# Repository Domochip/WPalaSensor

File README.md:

# WPalaSensor

This project aims to replace the Palazzetti (Fumis) room temperature sensor by an electronic simulator.  
It allows you to push home automation temperature to the stove.  
You can then keep native modulation that reduce power automatically when desired temperature is reached.  

## Compatibility

It appears that Fumis Controller is used by those brands for their stoves : 

* Palazzetti (All)
* Jotul
* TurboFonte
* Godin
* Fonte Flamme
* Invicta

If you have this controller in your stove, it's likely to be compatible.  

## Build your adapter

All files are inside `schematic` subfolder and has been designed with KiCad (free and open source)

### Schematic

### PCB

*We produced a small batch of this adapter for test/debugging and our personal use.
If you are interested, please PM.*

### Print your box

Box project (Fusion 360 & STL) can be found into `box` folder

### Code/Compile/Flash

Source code can be compiled using VisualStudioCode/Platformio and flashed onto a D1 Mini  
Or  
Download latest release in Release section

### Connect

⚠️To connect WPalaSensor to your stove, you need to be very carefull about the polarity⚠️.  
Here is the polarity of two possible temperature sensors on Fumis motherboard:

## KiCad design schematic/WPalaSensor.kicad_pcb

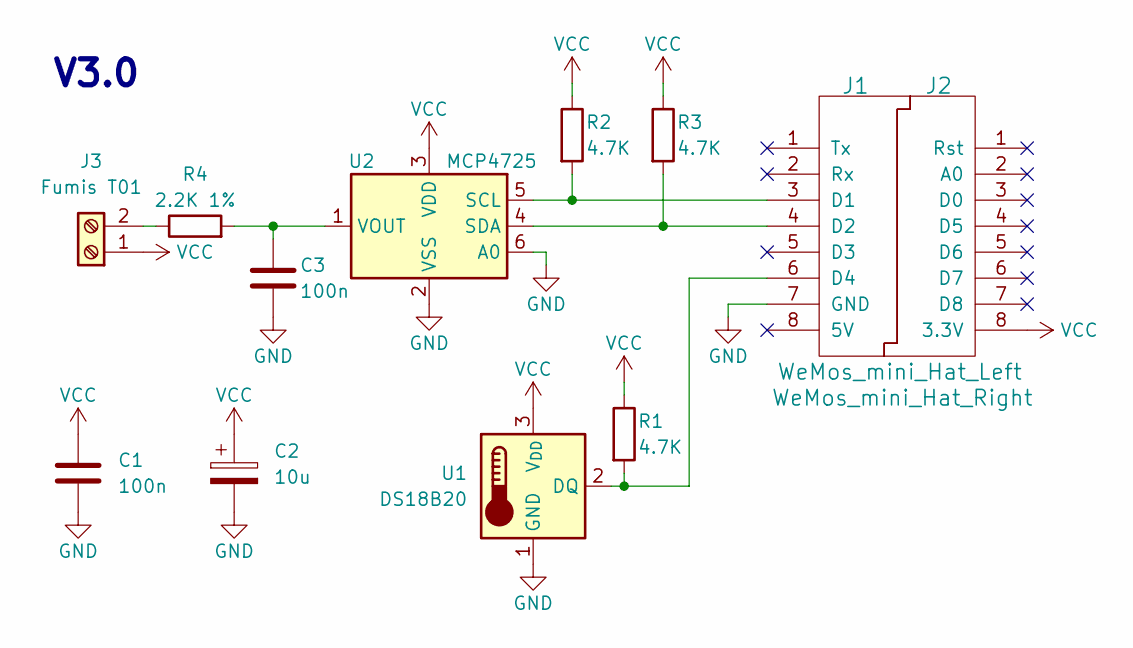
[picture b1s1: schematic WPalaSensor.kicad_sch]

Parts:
C1, C3: 100n; C_0805_2012Metric_Pad1.18x1.45mm_HandSolder; LCSC C49678
C2: 10u; CP_EIA-3216-18_Kemet-A_Pad1.58x1.35mm_HandSolder; LCSC C7171
J1: WeMos_mini_Hat_Left; WeMos_D1_mini_Hat_Left; LCSC C7509515
J2: WeMos_mini_Hat_Right; WeMos_D1_mini_Hat_Right; LCSC C7509515
J3: Fumis T01; TerminalBlock_bornier-2_P5.08mm; LCSC C474881
R1, R2, R3: 4.7K; R_0805_2012Metric_Pad1.20x1.40mm_HandSolder; LCSC C17673
R4: 2.2K 1%; R_0805_2012Metric_Pad1.20x1.40mm_HandSolder; LCSC C17520
U1: DS18B20; PinHeader_1x03_P2.54mm_Vertical
U2: MCP4725; SOT-23-6_Handsoldering; LCSC C144198

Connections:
GND: C1.2, C2.2, C3.2, J1.7 (GND), U1.1 (GND), U2.2 (VSS), U2.6 (A0)
unnamed: J1.3 (D1), R2.2, U2.5 (SCL)
unnamed: J1.4 (D2), R3.2, U2.4 (SDA)
unnamed: J1.6 (D4), R1.2, U1.2 (DQ)
unnamed: J3.2, R4.1
unnamed: C3.1, R4.2, U2.1 (VOUT)
VCC: C1.1, C2.1, J2.8 (3.3V), J3.1, R1.1, R2.1, R3.1, U1.3 (V_{DD}), U2.3 (VDD)

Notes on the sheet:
V3.0

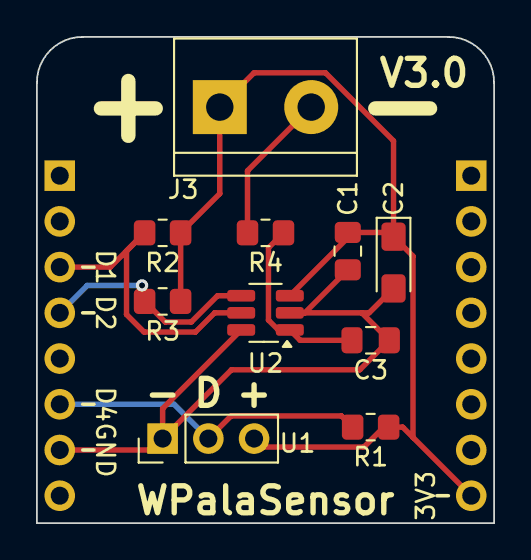
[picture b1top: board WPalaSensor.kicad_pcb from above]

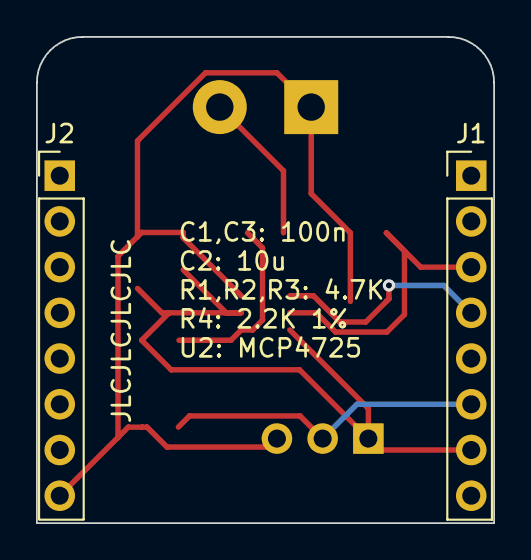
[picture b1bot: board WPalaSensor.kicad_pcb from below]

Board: 2 copper layers, 25.4 x 27.0 mm, 12 parts (2 on the bottom side), 7 nets.

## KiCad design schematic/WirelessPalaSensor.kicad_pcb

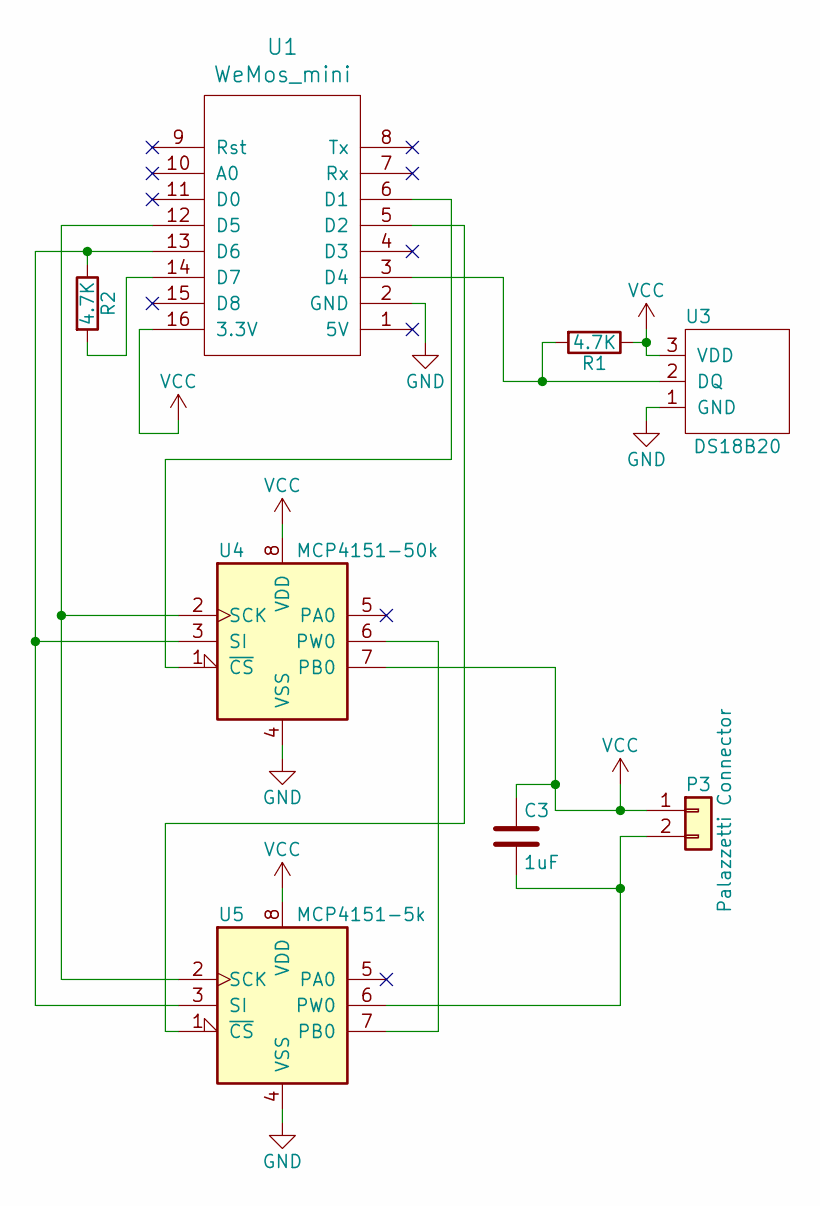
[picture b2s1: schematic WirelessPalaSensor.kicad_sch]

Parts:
C3: 1uF; C_0805_HandSoldering
P3: Palazzetti Connector; bornier2
R1, R2: 4.7K; R_0805_HandSoldering
U1: WeMos_mini; wemos-d1-mini-DIL-only
U3: DS18B20; Pin_Header_Straight_1x03_Pitch2.54mm
U4: MCP4151-50k; DIP-8_W7.62mm_LongPads
U5: MCP4151-5k; DIP-8_W7.62mm_LongPads

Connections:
GND: U1.2 (GND), U3.1 (GND), U4.4 (VSS), U5.4 (VSS)
unnamed: C3.2, P3.2, U5.6 (PW0)
unnamed: R1.2, U1.3 (D4), U3.2 (DQ)
unnamed: R2.1, U1.13 (D6), U4.3 (SI), U5.3 (SI)
unnamed: R2.2, U1.14 (D7)
unnamed: U1.5 (D2), U5.1 (~CS)
unnamed: U1.6 (D1), U4.1 (~CS)
unnamed: U1.12 (D5), U4.2 (SCK), U5.2 (SCK)
unnamed: U4.6 (PW0), U5.7 (PB0)
VCC: C3.1, P3.1, R1.1, U1.16 (3.3V), U3.3 (VDD), U4.7 (PB0), U4.8 (VDD), U5.8 (VDD)

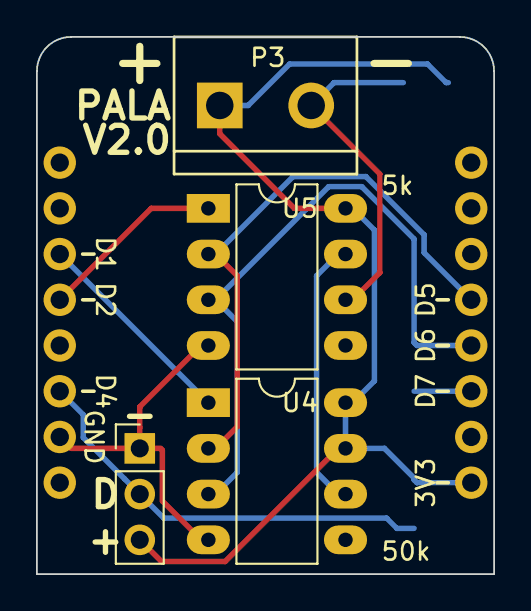
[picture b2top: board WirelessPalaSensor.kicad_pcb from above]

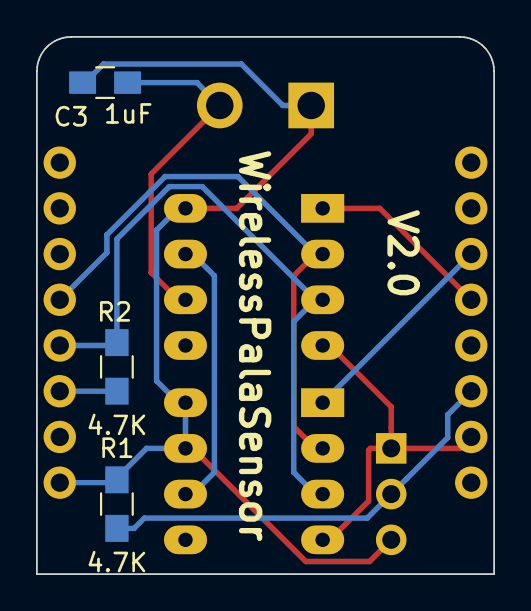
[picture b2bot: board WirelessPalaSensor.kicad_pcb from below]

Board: 2 copper layers, 25.4 x 29.8 mm, 8 parts (4 on the bottom side), 10 nets.

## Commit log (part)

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2024-10-25 Adapt code for Base 2.3.11
2024-10-25 Bump version to 4.1.0
2024-10-25 Factorize calibrator buttons code
2024-10-25 Adjust style of Step1 title
2024-10-25 Comments
2024-10-25 Keep only esp8266 for the moment
2024-10-28 Adapt code for Base 2.4.2
2024-10-28 Save RAM
2024-10-28 Formatiing
2024-10-29 Rename publishHassDiscoveryToMqtt to mqttPublishHassDiscovery
2024-10-29 Use new MQTTMan getStateString() method
2024-10-29 Add structure to publish update to mqtt
2024-10-29 Adapt code for Base 2.4.5
2024-10-29 Implement Update publishing
2024-10-29 Bump version to 4.1.1
2024-10-29 Move pushish of update to the right place
2024-10-29 Rename some properties and methods
2024-10-29 Publish Update will be retiried if MQTT was not connected
2024-10-29 Better handling of first refresh execution
2024-10-29 Adapt code for Base 2.4.7
2024-10-29 Adapt code for Base 2.4.8
2024-10-30 Adapt code for Base 2.4.10
2024-10-30 Adapt code for Base 2.4.11
2024-10-30 Adapt code for Base 2.4.12
2024-10-31 Adapt code for Base 2.4.14
2024-11-01 Simplify default AP password
2024-11-01 Fix default AP password
2024-11-01 subscript mqtt update topic
2024-11-01 First version of Online Update via MQTT
2024-11-01 Adapt code for Base 2.4.16
2024-11-01 Use SystemState::shouldReboot
2024-11-01 Publish one progress per second
2024-11-01 cleanup debug logging
2024-11-01 Update from MQTT (#4)
    * subscript mqtt update topic
    * First version of Online Update via MQTT
    * Use SystemState::shouldReboot
    * Publish one progress per second
    * cleanup debug logging
2024-11-01 Bump version to 4.1.2
2024-11-01 Improve init/reInit refresh and publishUpdate
2024-11-01 Remove some useless controls
2024-11-01 Make code more generic
2024-11-01 Adapt code for Base 2.4.18
2024-11-03 Bump version to 4.1.3
2024-11-04 Bump version to 4.1.4
2024-11-07 Implement new Home Assistant Update progress
2024-11-08 Hass 2024.11 update progress (#5)
    * Implement new Home Assistant Update progress
    * Update README.md
2024-11-09 Update schematic and libraries
2024-11-09 Remove DigiPot lib
2024-11-09 Create Mcp4725 class
2024-11-10 Add version to schematic
2024-11-10 Add R4
2024-11-10 Start using a readily available library for MCP4725
2024-11-10 Replace setDualDigiPot functions by setDAC functions
2024-11-10 Adapt appInitWebServer function for DAC
2024-11-11 Continue replacement of DigiPots to DAC
2024-11-11 Remove Digipot variables
2024-11-11 Add EEPROM param
2024-11-11 Init DAC
2024-11-11 Set default value of 20°C in EEPROM
2024-11-11 Update webpages
2024-11-11 Move DAC initialization
2024-11-11 Fix setDac code
2024-11-11 Fix inverted up and down button
2024-11-11 Add C3 capacitor
2024-11-11 Update schematic
2024-11-11 Update README.md images
2024-11-11 Update box
2024-11-11 Update box img
2024-11-26 Remove DigiPots pins
2024-11-27 Formatting
2024-11-30 Adjust default coeff values
2024-12-01 Fix local temp sensor not working (_tempSensorFound always false)
2024-12-01 Bump version to 4.1.5
2024-12-31 Copy MCP4725 lib locally
2024-12-31 Copy MCP4725 schematic symbol locally
2024-12-31 Update lib and symbol from MCP4725 to MCP4726
2024-12-31 Adjust schematic to use MCP4726
2025-01-02 Remove C3
2025-01-02 Update PCB according to new schematic
2025-01-03 Remove Power-Down and Reset/Wake-Up functions (tagged experimental)
2025-01-03 Remove Power-Down constants
2025-01-03 Remove General Call constants
2025-01-03 Remove Voltage functions
2025-01-03 Remove percentage functions
2025-01-03 Rename MCP4725 to MCP4726
2025-01-03 Remove _lastWriteEEPROM
2025-01-03 Comment
2025-01-03 Adjust reading of value in EEPROM
2025-01-03 Remove getAddress function
2025-01-03 Reorder functions
2025-01-03 Add VRef config constants
2025-01-03 Use bit shift for unicity
2025-01-03 Hardcode VRef for WPalaSensor
2026-04-06 Update schematic version
2026-04-07 New hw dac based (#6)
    * Update schematic and libraries
    * Remove DigiPot lib
    * Create Mcp4725 class
    * Add version to schematic
    * Add R4
    * Start using a readily available library for MCP4725
2026-04-07 Bump version to 4.2.0
2026-04-07 Switch to PubSubClient3 lib which is maintained
2026-04-09 box reworked
2026-04-11 Add polarity information
2026-05-13 Update to Kicad 10
2026-05-17 Adjust ConfigJSON and StatusJSON functions
2026-05-17 Adapt mqttPublishUpdate according to new parameters an type of fillLatestUpdateInfoJson
2026-05-17 use an httpBuffer to avoid String heap fragmentation
2026-05-17 use a buffer to render temperature strings to avoid heap fragmentation
2026-05-17 Simpler float conversion
2026-05-17 Reduce heap usage to avoid fragmentation
2026-05-17 Fix T1 pasing in JSON
2026-05-17 Use new MQTTMan::publish to reduce heap usage
2026-05-17 Reduce heap usage
2026-05-18 Adjust prepareTopic logic for Base 2.7.6
2026-05-18 Use new MQTTMan::publish signature
2026-05-18 Reduce String usage to avoid fragmentation
2026-05-18 Format
2026-05-18 Add default_entity_id for HomeAssistant
2026-05-18 There is a Cube Root function
2026-05-19 Adjust for Base 2.7.9
2026-05-20 Remove tempPassword variable
2026-05-20 Use new WifiMan::ipToCString helper
2026-05-21 Adjust for Base 2.7.11
2026-05-21 Adjust for Base 2.7.12
2026-05-21 Rename JsonDocument variables
2026-05-27 Update platformio.ini with post script and build flags
2026-05-27 Move default parameter value to header files instead of cpp
2026-05-27 Clean up getHTMLContent and getHTMLContentSize switch cases
2026-05-27 Use predefined JSON for fixed values in mqttPublishHassDiscovery
2026-05-27 Use predefined JSON for fixed values in mqttPublishUpdate
2026-05-28 Bump version to 4.3.1
2026-05-28 Adapt for Base 2.8.0
2026-05-28 Webpage includes moved from h file to cpp
2026-05-28 Adapt for Base 2.8.2
2026-05-28 Adapt for Base 2.9.0
2026-05-28 Remove index.html
2026-05-28 Add index.html to .gitignore
2026-05-29 Adapt for Base 2.9.4
2026-05-29 Move config validation code into validateConfig()
2026-05-29 Adapt for Base 2.9.6
2026-06-01 Bump version to 4.3.2
2026-06-03 Use WifiMan::getMacAddress()
2026-06-03 Move Update HomeAssistant entity to mqttPublishHassDiscovery
2026-06-03 HomeAssistant in_progress flag move to Base
2026-06-03 Minor Improvements
2026-06-06 use enum class instead of bunch of define
2026-06-06 Replace byte type by uint8_t for enum class
2026-06-06 finishing byte replacement by uint8_t
2026-06-07 Adapt for Base 2.9.10
2026-06-07 Refactor Steinhart-Hart coefficients to individual variables for clarity
2026-06-11 Change module status is published on MQTT
2026-06-11 Add WiFi connection counter entity to MQTT discovery
2026-06-11 Add missing name for WiFi Connect Count entity
2026-06-11 Add MQTT connection count to status JSON
2026-06-11 Add MQTT connection counter entity to Hass discovery
2026-06-11 Use more helpers and factorize mqttPublishHassDiscovery
2026-06-11 first version of MQTT publish dispatch
2026-06-11 getAppIdName can now be protected and doesn't need param
2026-06-11 Implement Application::getMqttTopicSuffix()
2026-06-11 Move mqttPublishStatus to Application
2026-06-11 Fix getMqttTopicSuffix
2026-06-11 Remove Application::getAppIdChar parameter
2026-06-12 Clean retained message on base topic in mqttConnectedCallback
2026-06-12 Refactor mqttPublishHassDiscovery to use HassDiscoveryCtx for improved context management
2026-06-12 Adapt for Base 2.9.13
2026-06-12 Use new mqttPublishHassDiscovery simpler and more organized
2026-06-12 Small memory improvement
2026-06-12 To clean retained message, empty payload should be retained
2026-06-12 Adapt for Base 2.10.1
2026-06-13 Adapt for Base 2.10.2
2026-06-15 Adapt for Base 2.10.3
2026-06-15 Bump version to 4.3.3
2026-06-15 Adapt for Base 2.10.5
2026-06-15 Add MQTT last disconnect reason to status JSON
2026-06-15 Add MQTT last disconnection reason to Home Assistant Discovery
2026-06-16 Update MQTT last disconnection reason icon in Home Assistant Discovery
2026-06-16 redirectWhenReachable can be called directly instead of using loadScript
2026-06-17 Add Temperature Fallback binary sensor entity to MQTT discovery
2026-06-17 Bump version to 4.3.4
2026-06-17 Reduce MQTT buffer size to 512 bytes
2026-06-17 Remove maxFailedRequest variable not used anymore
2026-06-17 Extract HTTP fetch code from refresh method
2026-06-17 Return NAN for temperature read failures instead of a placeholder value
2026-06-18 Refactor SingleDS18B20 class to use OneWire instance instead of inheritance
2026-06-18 Clarify sensor detection and avoid confusion
2026-06-18 Cleaner loop termination in readScratchPad method
2026-06-18 Don't need to pass addr because only _owROMCode is used
2026-06-18 Replace byte type by uint8_t
2026-06-18 Comments and format
2026-06-18 Improve readScratchPad
2026-06-18 Use float literal for division in readTemp method
2026-06-18 Fix overflow during time comparison
2026-06-18 Refactor temperature rounding to use roundTenth function for consistency
2026-06-18 C++ style struct
2026-06-18 Set default values upon construction
2026-06-18 Remove default values from header
2026-06-18 Simplify parseConfigJSON and fillConfigJSON
2026-06-18 Adapt for Base 2.10.9
2026-06-18 Adapt for Base 2.10.10
2026-06-19 Adapt for Base 2.10.11
